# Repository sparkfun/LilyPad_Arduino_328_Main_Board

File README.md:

SparkFun LilyPad Arduino 328 Main Board
=======================================
![SparkFun LilyPad Arduino 328 Main Board
](https://cdn.sparkfun.com//assets/parts/2/7/6/2/09266-01.jpg)

[*SparkFun LilyPad Arduino 328 Main Board
 (DEV-09266)*](https://www.sparkfun.com/products/9266)

This is LilyPad Arduino - the main board consisting of an ATmega328 with the Arduino bootloader and a minimum number of external components to keep it as small (and as simple) as possible. Board will run from 2V to 5V. 

Repository Contents
-------------------

* **/Hardware** - All Eagle design files (.brd, .sch)
License Information
-------------------
The hardware is released under [Creative Commons ShareAlike 4.0 International](https://creativecommons.org/licenses/by-sa/4.0/).

Distributed as-is; no warranty is given.

_A portion of this sale is given back to Dr. Leah Buechley for continued development and education of e-textiles and also to Arduino LLC to help fund continued development of new tools and new IDE features._

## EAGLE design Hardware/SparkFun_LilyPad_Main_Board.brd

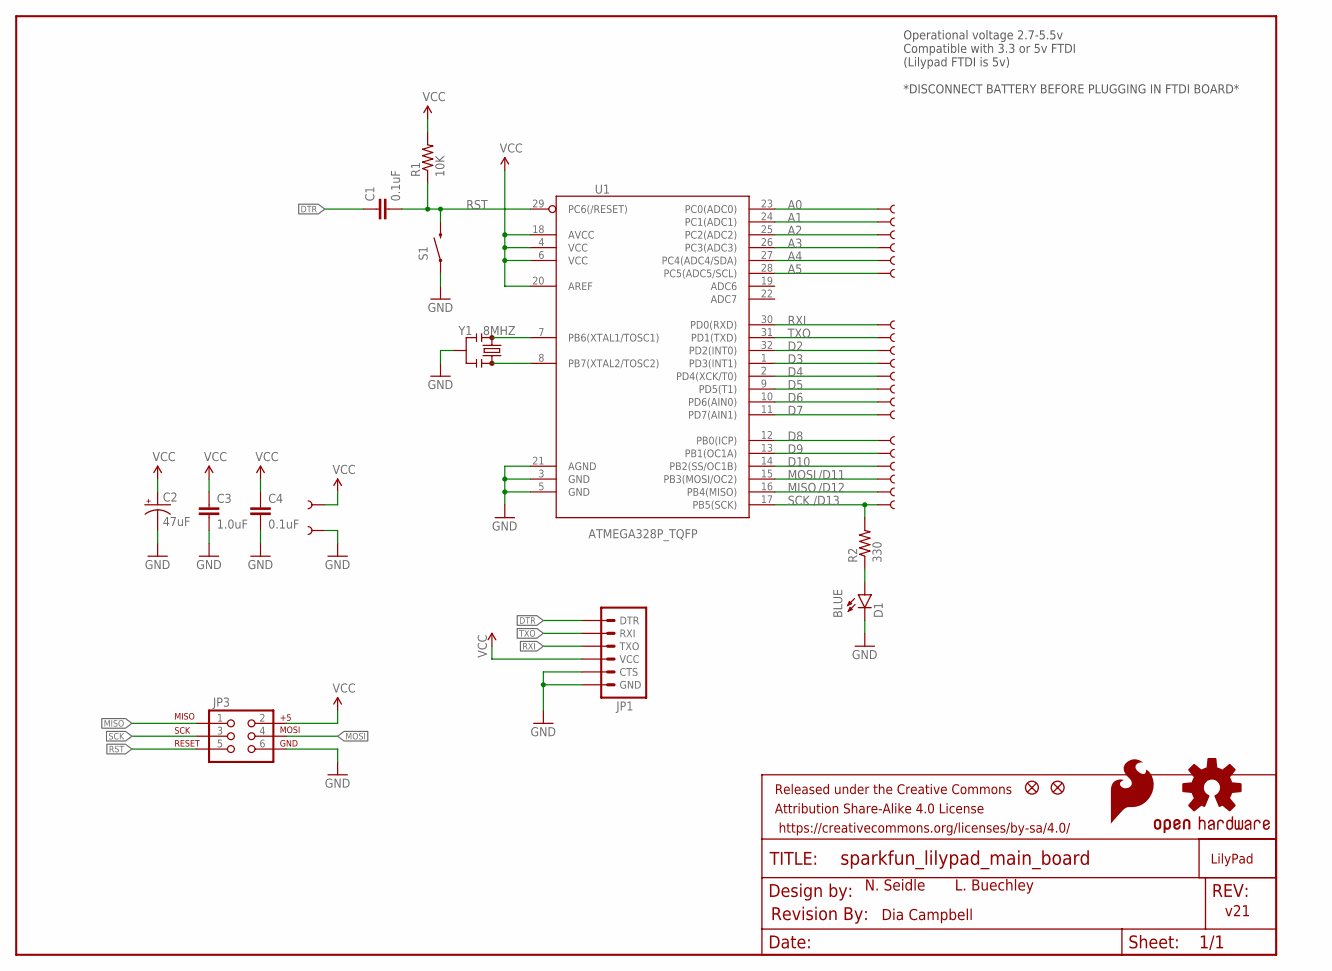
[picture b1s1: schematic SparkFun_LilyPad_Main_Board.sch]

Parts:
$0000003: LOGO-LPLPA; LOGO-LPA
C1, C4: 0.1uF; 0603-CAP
C2: 47uF; EIA3528
C3: 1.0uF; 0603-CAP
D1: BLUE; LED-0603
FID1, FID2: FIDUCIALUFIDUCIAL; MICRO-FIDUCIAL
FRAME1: FRAME-LETTER; CREATIVE_COMMONS
GND: SEWTAP9; PETAL-LONG-1-2SIDE
JP1: ARDUINO_SERIAL_PROGRAMSMD; 1X06-SMD
JP3: FEMALE 2x3; 2X3-NS
LOGO1: SFE_LOGO_FLAME.3COP; SFE_LOGO_FLAME_COPPER_.3
LOGO2: OSHW-LOGO-COPPERM; OSHW-LOGO-M
R1: 10K; 0603-RES
R2: 330; 0603-RES
S1: SWITCH-MOMENTARY-2SMD-REDUNDANT; TACTILE-SWITCH-SMD
U1: ATMEGA328P_TQFP; TQFP32-08
U$1, U$2, U$3, U$4, U$5, U$6, U$7, U$8, U$9, U$10, U$11, U$12, U$13, U$14, U$15, U$16, U$17, U$18, U$19, U$20, U$21: SEWTAP9; PETAL-LONG-1-2SIDE
U$22: REVISION
Y1: 8MHZ; RESONATOR-SMD

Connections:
A0: U1.23 (PC0(ADC0)), U$1.1
A1: U1.24 (PC1(ADC1)), U$2.1
A2: U1.25 (PC2(ADC2)), U$3.1
A3: U1.26 (PC3(ADC3)), U$4.1
A4: U1.27 (PC4(ADC4/SDA)), U$5.1
A5: U1.28 (PC5(ADC5/SCL)), U$6.1
D2: U1.32 (PD2(INT0)), U$9.1
D3: U1.1 (PD3(INT1)), U$10.1
D4: U1.2 (PD4(XCK/T0)), U$11.1
D5: U1.9 (PD5(T1)), U$12.1
D6: U1.10 (PD6(AIN0)), U$13.1
D7: U1.11 (PD7(AIN1)), U$14.1
D8: U1.12 (PB0(ICP)), U$15.1
D9: U1.13 (PB1(OC1A)), U$16.1
D10: U1.14 (PB2(SS/OC1B)), U$17.1
DTR: C1.1, JP1.1 (DTR)
GND: C2.C (-), C3.2, C4.2, D1.C, GND.1, JP1.5 (CTS), JP1.6 (GND), JP3.6, S1.1, S1.2 (1), U1.3 (GND), U1.5 (GND), U1.21 (AGND), Y1.2
MISO: JP3.1, U1.16 (PB4(MISO)), U$19.1
MOSI: JP3.4, U1.15 (PB3(MOSI/OC2)), U$18.1
unnamed: U1.7 (PB6(XTAL1/TOSC1)), Y1.1
unnamed: D1.A, R2.1
unnamed: U1.8 (PB7(XTAL2/TOSC2)), Y1.3
RST: C1.2, JP3.5, R1.1, S1.3 (2), S1.4 (2), U1.29 (PC6(/RESET))
RXI: JP1.3 (TXO), U1.30 (PD0(RXD)), U$7.1
SCK: JP3.3, R2.2, U1.17 (PB5(SCK)), U$21.1
TXO: JP1.2 (RXI), U1.31 (PD1(TXD)), U$8.1
VCC: C2.A (+), C3.1, C4.1, JP1.4 (VCC), JP3.2, R1.2, U1.4 (VCC), U1.6 (VCC), U1.18 (AVCC), U1.20 (AREF), U$20.1

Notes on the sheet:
/D11
/D12
/D13
L. Buechley
N. Seidle
Dia Campbell
v21
Operational voltage 2.7-5.5v Compatible with 3.3 or 5v FTDI (Lilypad FTDI is 5v) *DISCONNECT BATTERY BEFORE PLUGGING IN FTDI BOARD*

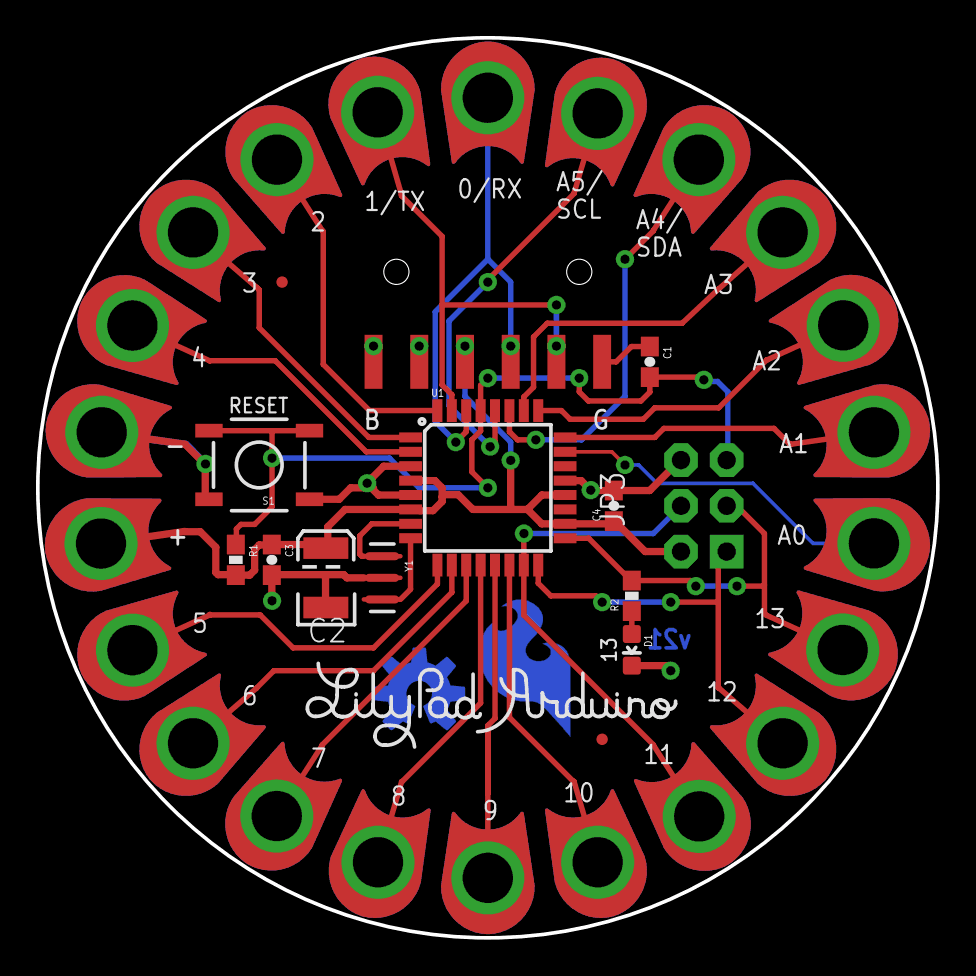
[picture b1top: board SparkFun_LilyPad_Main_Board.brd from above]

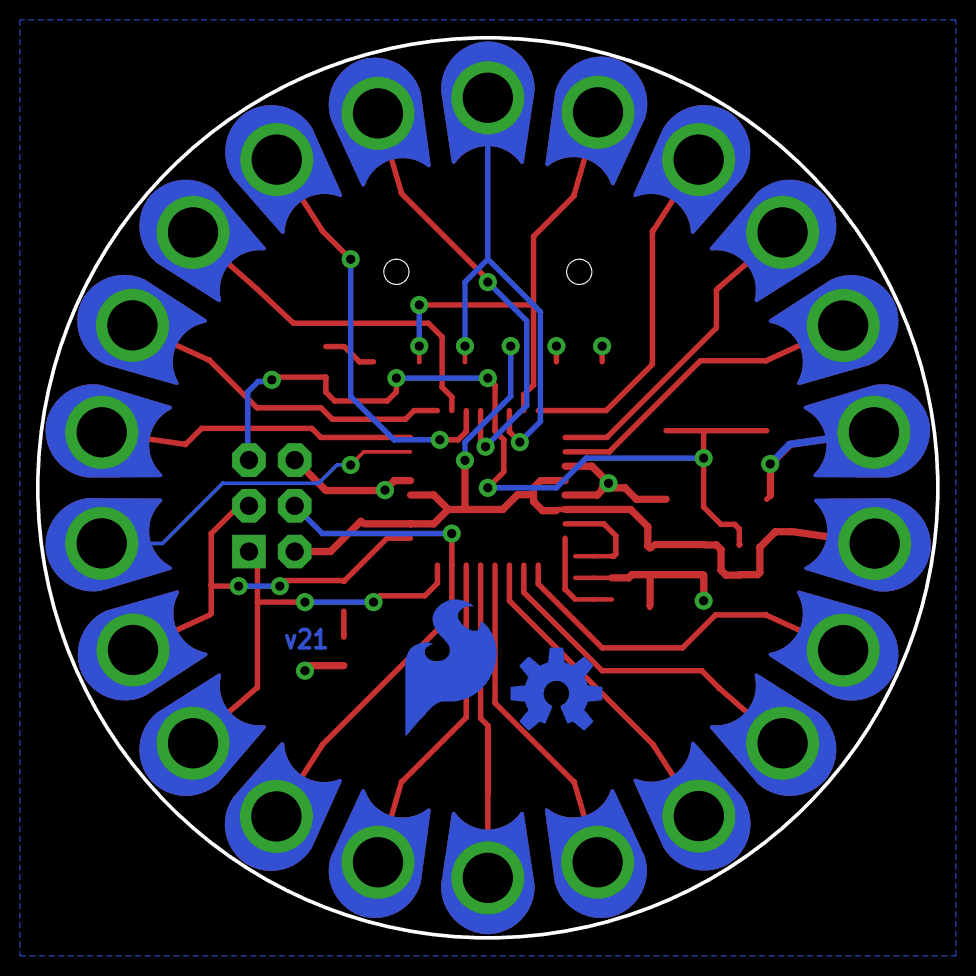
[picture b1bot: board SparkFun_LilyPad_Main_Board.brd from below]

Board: 2 copper layers, 50.0 x 50.0 mm, 41 parts (2 on the bottom side), 27 nets.

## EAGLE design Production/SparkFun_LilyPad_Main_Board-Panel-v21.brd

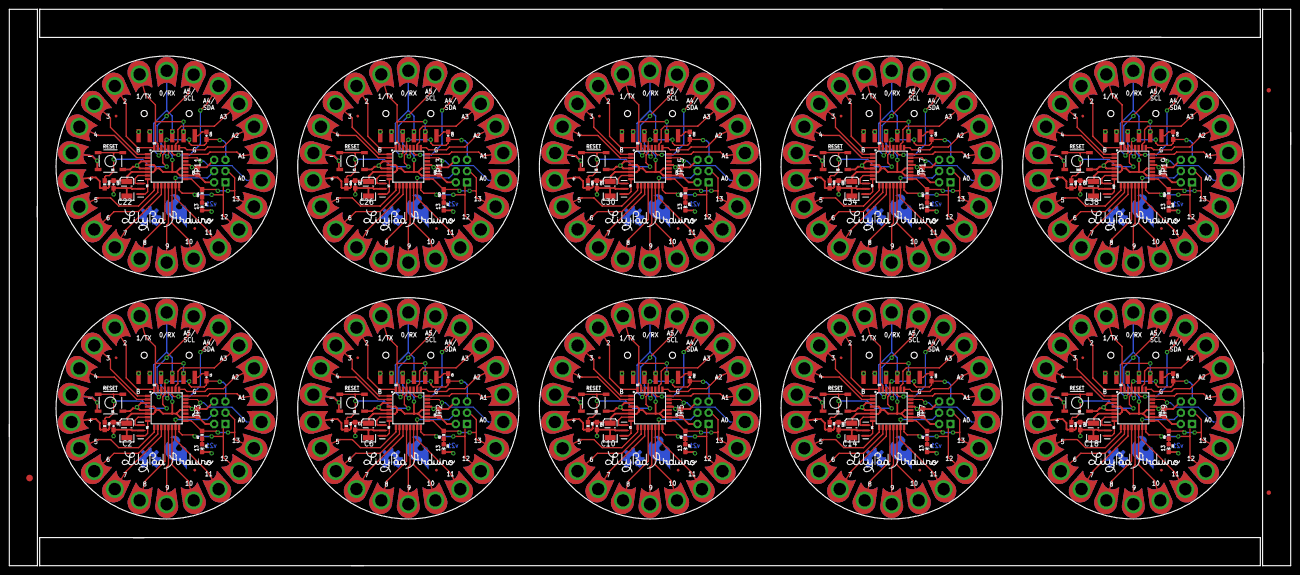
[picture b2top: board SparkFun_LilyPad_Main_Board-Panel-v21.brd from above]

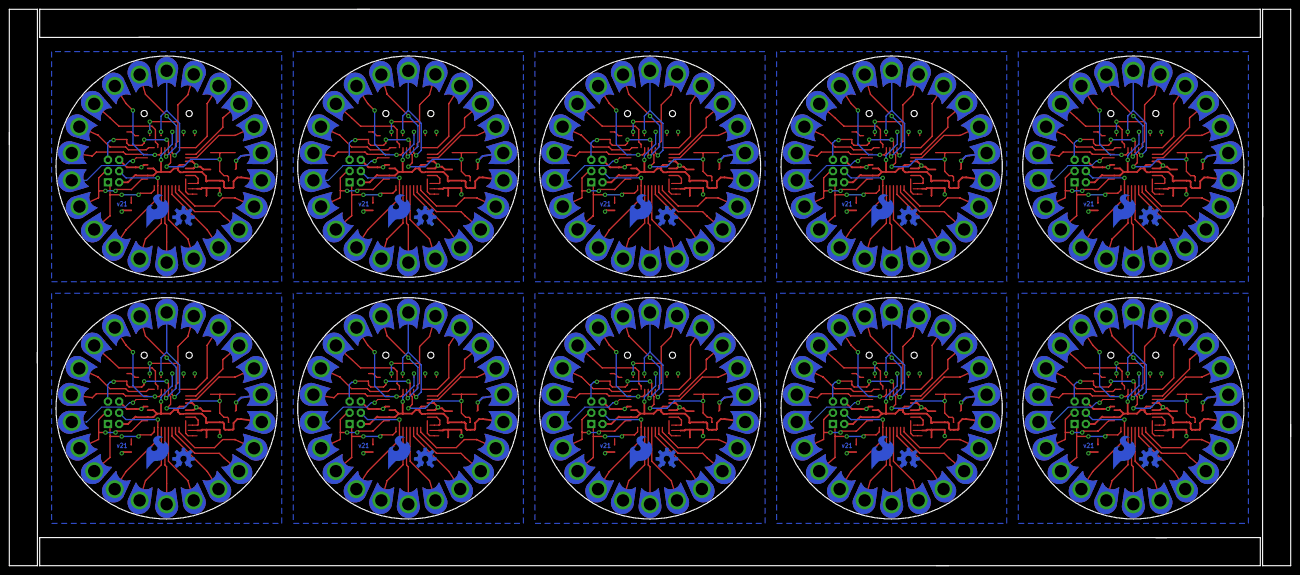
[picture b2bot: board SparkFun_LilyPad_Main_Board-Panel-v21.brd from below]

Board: 2 copper layers, 289.6 x 125.7 mm, 393 parts (20 on the bottom side), 270 nets.

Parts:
$0000001, $0000002, $0000003, $0000004, $0000005, $0000006, $0000007, $0000008, $0000009, $0000010: LOGO-LPLPA; LOGO-LPA
C1, C4, C5, C8, C9, C12, C13, C16, C17, C20, C21, C24, C25, C28, C29, C32, C33, C36, C37, C40: 0.1uF; 0603-CAP
C2, C6, C10, C14, C18, C22, C26, C30, C34, C38: 47uF; EIA3528
C3, C7, C11, C15, C19, C23, C27, C31, C35, C39: 1.0uF; 0603-CAP
D1, D2, D3, D4, D5, D6, D7, D8, D9, D10: BLUE; LED-0603
E$1: FIDUCIAL-1.5X3
E$7, E$8: FIDUCIAL-1X2
FID1, FID2, FID3, FID4, FID5, FID6, FID7, FID8, FID9, FID10, FID11, FID12, FID13, FID14, FID15, FID16, FID17, FID18, FID19, FID20: FIDUCIALUFIDUCIAL; MICRO-FIDUCIAL
GND, GND1, GND2, GND3, GND4, GND5, GND6, GND7, GND8, GND9: SEWTAP9; PETAL-LONG-1-2SIDE
JP1, JP4, JP6, JP8, JP10, JP12, JP14, JP16, JP18, JP20: 1X06-SMD
JP2, JP3, JP5, JP7, JP9, JP11, JP13, JP15, JP17, JP19: FEMALE 2x3; 2X3-NS
LOGO1, LOGO3, LOGO5, LOGO7, LOGO9, LOGO11, LOGO13, LOGO15, LOGO17, LOGO19: SFE_LOGO_FLAME.3COP; SFE_LOGO_FLAME_COPPER_.3
LOGO2, LOGO4, LOGO6, LOGO8, LOGO10, LOGO12, LOGO14, LOGO16, LOGO18, LOGO20: OSHW-LOGO-COPPERM; OSHW-LOGO-M
R1, R4, R6, R8, R10, R12, R14, R16, R18, R20: 10K; 0603-RES
R2, R3, R5, R7, R9, R11, R13, R15, R17, R19: 330; 0603-RES
S1, S2, S3, S4, S5, S6, S7, S8, S9, S10: SWITCH-MOMENTARY-2SMD-REDUNDANT; TACTILE-SWITCH-SMD
U1, U2, U3, U4, U5, U6, U7, U8, U9, U10: ATMEGA328P_TQFP; TQFP32-08
U$1, U$2, U$3, U$4, U$5, U$6, U$7, U$8, U$9, U$10, U$11, U$12, U$13, U$14, U$15, U$16, U$17, U$18, U$19, U$20, U$21, U$22, U$23, U$24, U$25, U$26, U$27, U$28, U$29, U$30, U$31, U$32, U$33, U$34, U$35, U$36, U$37, U$38, U$39, U$40, U$41, U$42, U$43, U$44, U$45, U$46, U$47, U$48, U$49, U$50, U$51, U$52, U$53, U$54, U$55, U$56, U$57, U$58, U$59, U$60, U$61, U$62, U$63, U$64, U$65, U$66, U$67, U$68, U$69, U$70, U$71, U$72, U$73, U$74, U$75, U$76, U$77, U$78, U$79, U$80, U$81, U$82, U$83, U$84, U$85, U$86, U$87, U$88, U$89, U$90, U$91, U$92, U$93, U$94, U$95, U$96, U$97, U$98, U$99, U$100, U$101, U$102, U$103, U$104, U$105, U$106, U$107, U$108, U$109, U$110, U$111, U$112, U$113, U$114, U$115, U$116, U$117, U$118, U$119, U$120, U$121, U$122, U$123, U$124, U$125, U$126, U$127, U$128, U$129, U$130, U$131, U$132, U$133, U$134, U$135, U$136, U$137, U$138, U$139, U$140, U$141, U$142, U$143, U$144, U$145, U$146, U$147, U$148, U$149, U$150, U$151, U$152, U$153, U$154, U$155, U$156, U$157, U$158, U$159, U$160, U$161, U$162, U$163, U$164, U$165, U$166, U$167, U$168, U$169, U$170, U$171, U$172, U$173, U$174, U$175, U$176, U$177, U$178, U$179, U$180, U$181, U$182, U$183, U$184, U$185, U$186, U$187, U$188, U$189, U$190, U$191, U$192, U$193, U$194, U$195, U$196, U$197, U$198, U$199, U$200, U$201, U$202, U$203, U$204, U$205, U$206, U$207, U$208, U$209, U$210: SEWTAP9; PETAL-LONG-1-2SIDE
Y1, Y2, Y3, Y4, Y5, Y6, Y7, Y8, Y9, Y10: 8MHZ; RESONATOR-SMD

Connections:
A0: U1.23, U$1.1
A1: U1.24, U$2.1
A2: U1.25, U$3.1
A3: U1.26, U$4.1
A4: U1.27, U$5.1
A5: U1.28, U$6.1
A6: U2.23, U$42.1
A7: U2.24, U$22.1
A8: U2.25, U$23.1
A9: U2.26, U$24.1
A10: U2.27, U$25.1
A11: U2.28, U$26.1
A12: U3.23, U$63.1
A13: U3.24, U$43.1
A14: U3.25, U$44.1
A15: U3.26, U$45.1
A16: U3.27, U$46.1
A17: U3.28, U$47.1
A18: U4.23, U$84.1
A19: U4.24, U$64.1
A20: U4.25, U$65.1
A21: U4.26, U$66.1
A22: U4.27, U$67.1
A23: U4.28, U$68.1
A24: U5.23, U$105.1
A25: U5.24, U$85.1
A26: U5.25, U$86.1
A27: U5.26, U$87.1
A28: U5.27, U$88.1
A29: U5.28, U$89.1
A30: U6.23, U$126.1
A31: U6.24, U$106.1
A32: U6.25, U$107.1
A33: U6.26, U$108.1
A34: U6.27, U$109.1
A35: U6.28, U$110.1
A36: U7.23, U$147.1
A37: U7.24, U$127.1
A38: U7.25, U$128.1
A39: U7.26, U$129.1
A40: U7.27, U$130.1
A41: U7.28, U$131.1
A42: U8.23, U$168.1
A43: U8.24, U$148.1
A44: U8.25, U$149.1
A45: U8.26, U$150.1
A46: U8.27, U$151.1
A47: U8.28, U$152.1
A48: U9.23, U$189.1
A49: U9.24, U$169.1
A50: U9.25, U$170.1
A51: U9.26, U$171.1
A52: U9.27, U$172.1
A53: U9.28, U$173.1
A54: U10.23, U$210.1
A55: U10.24, U$190.1
A56: U10.25, U$191.1
A57: U10.26, U$192.1
A58: U10.27, U$193.1
A59: U10.28, U$194.1
D1: U2.32, U$37.1
D2: U1.32, U$9.1
D3: U1.1, U$10.1
D4: U1.2, U$11.1
D5: U1.9, U$12.1
D6: U1.10, U$13.1
D7: U1.11, U$14.1
D8: U1.12, U$15.1
D9: U1.13, U$16.1
D10: U1.14, U$17.1
D11: U2.1, U$36.1
D12: U2.2, U$35.1
D13: U2.9, U$34.1
D14: U2.10, U$33.1
D15: U2.12, U$27.1
D16: U2.14, U$29.1
D17: U2.11, U$40.1
D18: U2.13, U$28.1
D19: U3.32, U$58.1
D20: U3.1, U$57.1
D21: U3.2, U$56.1
D22: U3.9, U$55.1
D23: U3.10, U$54.1
D24: U3.12, U$48.1
D25: U3.14, U$50.1
D26: U3.11, U$61.1
D27: U3.13, U$49.1
D28: U4.32, U$79.1
D29: U4.1, U$78.1
D30: U4.2, U$77.1
D31: U4.9, U$76.1
D32: U4.10, U$75.1
D33: U4.12, U$69.1
D34: U4.14, U$71.1
D35: U4.11, U$82.1
D36: U4.13, U$70.1
D37: U5.32, U$100.1
D38: U5.1, U$99.1
D39: U5.2, U$98.1
D40: U5.9, U$97.1
D41: U5.10, U$96.1
D42: U5.12, U$90.1
D43: U5.14, U$92.1
D44: U5.11, U$103.1
D45: U5.13, U$91.1
D46: U6.32, U$121.1
D47: U6.1, U$120.1
D48: U6.2, U$119.1
D49: U6.9, U$118.1
D50: U6.10, U$117.1
D51: U6.12, U$111.1
D52: U6.14, U$113.1
D53: U6.11, U$124.1
D54: U6.13, U$112.1
D55: U7.32, U$142.1
D56: U7.1, U$141.1
D57: U7.2, U$140.1
D58: U7.9, U$139.1
D59: U7.10, U$138.1
D60: U7.12, U$132.1
D61: U7.14, U$134.1
D62: U7.11, U$145.1
D63: U7.13, U$133.1
D64: U8.32, U$163.1
D65: U8.1, U$162.1
D66: U8.2, U$161.1
D67: U8.9, U$160.1
D68: U8.10, U$159.1
D69: U8.12, U$153.1
D70: U8.14, U$155.1
D71: U8.11, U$166.1
D72: U8.13, U$154.1
D73: U9.32, U$184.1
D74: U9.1, U$183.1
D75: U9.2, U$182.1
D76: U9.9, U$181.1
D77: U9.10, U$180.1
D78: U9.12, U$174.1
D79: U9.14, U$176.1
D80: U9.11, U$187.1
D81: U9.13, U$175.1
D82: U10.32, U$205.1
D83: U10.1, U$204.1
D84: U10.2, U$203.1
D85: U10.9, U$202.1
D86: U10.10, U$201.1
D87: U10.12, U$195.1
D88: U10.14, U$197.1
D89: U10.11, U$208.1
D90: U10.13, U$196.1
DTR: C1.1, JP1.1
DTR1: C8.1, JP4.1
DTR2: C12.1, JP6.1
DTR3: C16.1, JP8.1
DTR4: C20.1, JP10.1
DTR5: C24.1, JP12.1
DTR6: C28.1, JP14.1
DTR7: C32.1, JP16.1
DTR8: C36.1, JP18.1
DTR9: C40.1, JP20.1
GND: C2.C, C3.2, C4.2, D1.C, GND.1, JP1.5, JP1.6, JP3.6, S1.1, S1.2, U1.3, U1.5, U1.21, Y1.2
GND1: C5.2, C6.C, C7.2, D2.C, GND1.1, JP2.6, JP4.5, JP4.6, S2.1, S2.2, U2.3, U2.5, U2.21, Y2.2
GND2: C9.2, C10.C, C11.2, D3.C, GND2.1, JP5.6, JP6.5, JP6.6, S3.1, S3.2, U3.3, U3.5, U3.21, Y3.2
GND3: C13.2, C14.C, C15.2, D4.C, GND3.1, JP7.6, JP8.5, JP8.6, S4.1, S4.2, U4.3, U4.5, U4.21, Y4.2
GND4: C17.2, C18.C, C19.2, D5.C, GND4.1, JP9.6, JP10.5, JP10.6, S5.1, S5.2, U5.3, U5.5, U5.21, Y5.2
GND5: C21.2, C22.C, C23.2, D6.C, GND5.1, JP11.6, JP12.5, JP12.6, S6.1, S6.2, U6.3, U6.5, U6.21, Y6.2
GND6: C25.2, C26.C, C27.2, D7.C, GND6.1, JP13.6, JP14.5, JP14.6, S7.1, S7.2, U7.3, U7.5, U7.21, Y7.2
GND7: C29.2, C30.C, C31.2, D8.C, GND7.1, JP15.6, JP16.5, JP16.6, S8.1, S8.2, U8.3, U8.5, U8.21, Y8.2
GND8: C33.2, C34.C, C35.2, D9.C, GND8.1, JP17.6, JP18.5, JP18.6, S9.1, S9.2, U9.3, U9.5, U9.21, Y9.2
GND9: C37.2, C38.C, C39.2, D10.C, GND9.1, JP19.6, JP20.5, JP20.6, S10.1, S10.2, U10.3, U10.5, U10.21, Y10.2
MISO: JP3.1, U1.16, U$19.1
MISO1: JP2.1, U2.16, U$31.1
MISO2: JP5.1, U3.16, U$52.1
MISO3: JP7.1, U4.16, U$73.1
MISO4: JP9.1, U5.16, U$94.1
MISO5: JP11.1, U6.16, U$115.1
MISO6: JP13.1, U7.16, U$136.1
MISO7: JP15.1, U8.16, U$157.1
MISO8: JP17.1, U9.16, U$178.1
MISO9: JP19.1, U10.16, U$199.1
MOSI: JP3.4, U1.15, U$18.1
MOSI1: JP2.4, U2.15, U$30.1
MOSI2: JP5.4, U3.15, U$51.1
MOSI3: JP7.4, U4.15, U$72.1
MOSI4: JP9.4, U5.15, U$93.1
MOSI5: JP11.4, U6.15, U$114.1
MOSI6: JP13.4, U7.15, U$135.1
MOSI7: JP15.4, U8.15, U$156.1
MOSI8: JP17.4, U9.15, U$177.1
MOSI9: JP19.4, U10.15, U$198.1
unnamed: U1.7, Y1.1
unnamed: D1.A, R2.1
unnamed: U1.8, Y1.3
unnamed: D2.A, R3.1
unnamed: U2.7, Y2.1
unnamed: U2.8, Y2.3
unnamed: D3.A, R5.1
unnamed: U3.7, Y3.1
unnamed: U3.8, Y3.3
unnamed: D4.A, R7.1
unnamed: U4.7, Y4.1
unnamed: U4.8, Y4.3
unnamed: D5.A, R9.1
unnamed: U5.7, Y5.1
unnamed: U5.8, Y5.3
unnamed: D6.A, R11.1
unnamed: U6.7, Y6.1
unnamed: U6.8, Y6.3
unnamed: D7.A, R13.1
unnamed: U7.7, Y7.1
unnamed: U7.8, Y7.3
unnamed: D8.A, R15.1
unnamed: U8.7, Y8.1
unnamed: U8.8, Y8.3
unnamed: D9.A, R17.1
unnamed: U9.7, Y9.1
unnamed: U9.8, Y9.3
unnamed: D10.A, R19.1
unnamed: U10.7, Y10.1
unnamed: U10.8, Y10.3
RST: C1.2, JP3.5, R1.1, S1.3, S1.4, U1.29
RST1: C8.2, JP2.5, R4.1, S2.3, S2.4, U2.29
RST2: C12.2, JP5.5, R6.1, S3.3, S3.4, U3.29
RST3: C16.2, JP7.5, R8.1, S4.3, S4.4, U4.29
RST4: C20.2, JP9.5, R10.1, S5.3, S5.4, U5.29
RST5: C24.2, JP11.5, R12.1, S6.3, S6.4, U6.29
RST6: C28.2, JP13.5, R14.1, S7.3, S7.4, U7.29
RST7: C32.2, JP15.5, R16.1, S8.3, S8.4, U8.29
RST8: C36.2, JP17.5, R18.1, S9.3, S9.4, U9.29
RST9: C40.2, JP19.5, R20.1, S10.3, S10.4, U10.29
RXI: JP1.3, U1.30, U$7.1
RXI1: JP4.3, U2.30, U$39.1
RXI2: JP6.3, U3.30, U$60.1
RXI3: JP8.3, U4.30, U$81.1
RXI4: JP10.3, U5.30, U$102.1
RXI5: JP12.3, U6.30, U$123.1
RXI6: JP14.3, U7.30, U$144.1
RXI7: JP16.3, U8.30, U$165.1
RXI8: JP18.3, U9.30, U$186.1
RXI9: JP20.3, U10.30, U$207.1
SCK: JP3.3, R2.2, U1.17, U$21.1
SCK1: JP2.3, R3.2, U2.17, U$32.1
SCK2: JP5.3, R5.2, U3.17, U$53.1
SCK3: JP7.3, R7.2, U4.17, U$74.1
SCK4: JP9.3, R9.2, U5.17, U$95.1
SCK5: JP11.3, R11.2, U6.17, U$116.1
SCK6: JP13.3, R13.2, U7.17, U$137.1
SCK7: JP15.3, R15.2, U8.17, U$158.1
SCK8: JP17.3, R17.2, U9.17, U$179.1
SCK9: JP19.3, R19.2, U10.17, U$200.1
TXO: JP1.2, U1.31, U$8.1
TXO1: JP4.2, U2.31, U$38.1
TXO2: JP6.2, U3.31, U$59.1
TXO3: JP8.2, U4.31, U$80.1
TXO4: JP10.2, U5.31, U$101.1
TXO5: JP12.2, U6.31, U$122.1
TXO6: JP14.2, U7.31, U$143.1
TXO7: JP16.2, U8.31, U$164.1
TXO8: JP18.2, U9.31, U$185.1
TXO9: JP20.2, U10.31, U$206.1
VCC: C2.A, C3.1, C4.1, JP1.4, JP3.2, R1.2, U1.4, U1.6, U1.18, U1.20, U$20.1
VCC1: C5.1, C6.A, C7.1, JP2.2, JP4.4, R4.2, U2.4, U2.6, U2.18, U2.20, U$41.1
VCC2: C9.1, C10.A, C11.1, JP5.2, JP6.4, R6.2, U3.4, U3.6, U3.18, U3.20, U$62.1
VCC3: C13.1, C14.A, C15.1, JP7.2, JP8.4, R8.2, U4.4, U4.6, U4.18, U4.20, U$83.1
VCC4: C17.1, C18.A, C19.1, JP9.2, JP10.4, R10.2, U5.4, U5.6, U5.18, U5.20, U$104.1
VCC5: C21.1, C22.A, C23.1, JP11.2, JP12.4, R12.2, U6.4, U6.6, U6.18, U6.20, U$125.1
VCC6: C25.1, C26.A, C27.1, JP13.2, JP14.4, R14.2, U7.4, U7.6, U7.18, U7.20, U$146.1
VCC7: C29.1, C30.A, C31.1, JP15.2, JP16.4, R16.2, U8.4, U8.6, U8.18, U8.20, U$167.1
VCC8: C33.1, C34.A, C35.1, JP17.2, JP18.4, R18.2, U9.4, U9.6, U9.18, U9.20, U$188.1
VCC9: C37.1, C38.A, C39.1, JP19.2, JP20.4, R20.2, U10.4, U10.6, U10.18, U10.20, U$209.1

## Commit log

2015-03-03 Hardware commit and README update
2015-03-13 Committing v21 hardware files
    Updated to 0603, fixed packages, schematic cleanup, and silk updates.
2015-03-26 Updates for QC checklist
2015-03-30 Moving logos to bottom copper, removed some silk
2015-03-30 Made pin 13 LED blue; current standard
2015-03-31 Moved info on schematic, added board color
2015-04-02 Corrected board thickness
2015-06-25 Silk change to I2C pins
    Leah's request
2015-06-30 Another silk change to I2C pins
2015-07-01 adjust silk for consistency
2015-09-02 created panel v21

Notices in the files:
parts and their libraries:
SparkFun-Aesthetics: Licensing: Creative Commons ShareAlike 4.0 International - https://creativecommons.org/licenses/by-sa/4.0
SparkFun-Aesthetics: Released under the Creative Commons Attribution Share-Alike 4.0 License
SparkFun-Aesthetics: Released under the Creative Commons
